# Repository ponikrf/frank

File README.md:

# FRANK

FRANK is a versatile hardware emulation platform based on Raspberry Pico and Raspberry Zero. It is a hardware fork of the [Murmulator](https://murmulator.ru/) project by [Alex Ekb](https://t.me/Alex_Eburg), incorporating numerous additional features.

The name "FRANK" is derived from "Frankenstein" as it integrates various components from different projects, similar to how Dr. Frankenstein created his monster from different parts. This combination enables FRANK to offer a unique and powerful set of capabilities.

## Supported Platforms

FRANK supports emulation for a variety of platforms, including:

* ZX Spectrum (48K, 128K and other models, including clones)
* IBM PC XT 8088
* BK-0011М (soviet 8 bit home computer)
* Radio 86RK (soviet 8 bit home computer)
* Atari 800
* NES/Famicom (also known as Dendy)
* Sega Master System
* Sega Game Gear
* NEC PC Engine / TurboGrafx 16
* Sega MegaDrive / Genesis
* Nintendo GameBoy
* Nintendo GameBoy Color
* Watara Supervision
* Atari Lynx
* Bandai Wonderswan
* NeoGeo Pocket Color
* Picomite MMBasic
* VersaTerm
* DOOM
* Macintosh 512K
* MurmulatorOS

## FRANK Models

Currently there are the following versions of FRANK available:

* [FRANK M1](./hardware/frank_m1) (latest hardware revision: 1.17)
* [FRANK M2](./hardware/frank_m2) (latest hardware revision: 1.03)
* [MiniFRANK RM1](./hardware/minifrank_rm1) (latest hardware revision: 2.07)
* [TurboFRANK](./hardware/turbofrank) (latest hardware revision: 1.07)

## Side Projects

* [HDMI2VGA](./hardware/hdmi2vga) - HDMI to VGA/Soft Composite passive adaptor (latest hardware revision: 2.03)
* [USB2PS2](./hardware/usb2ps2) - USB to PS/2 adapter built on RP2040-Zero (latest hardware revision: 1.03)

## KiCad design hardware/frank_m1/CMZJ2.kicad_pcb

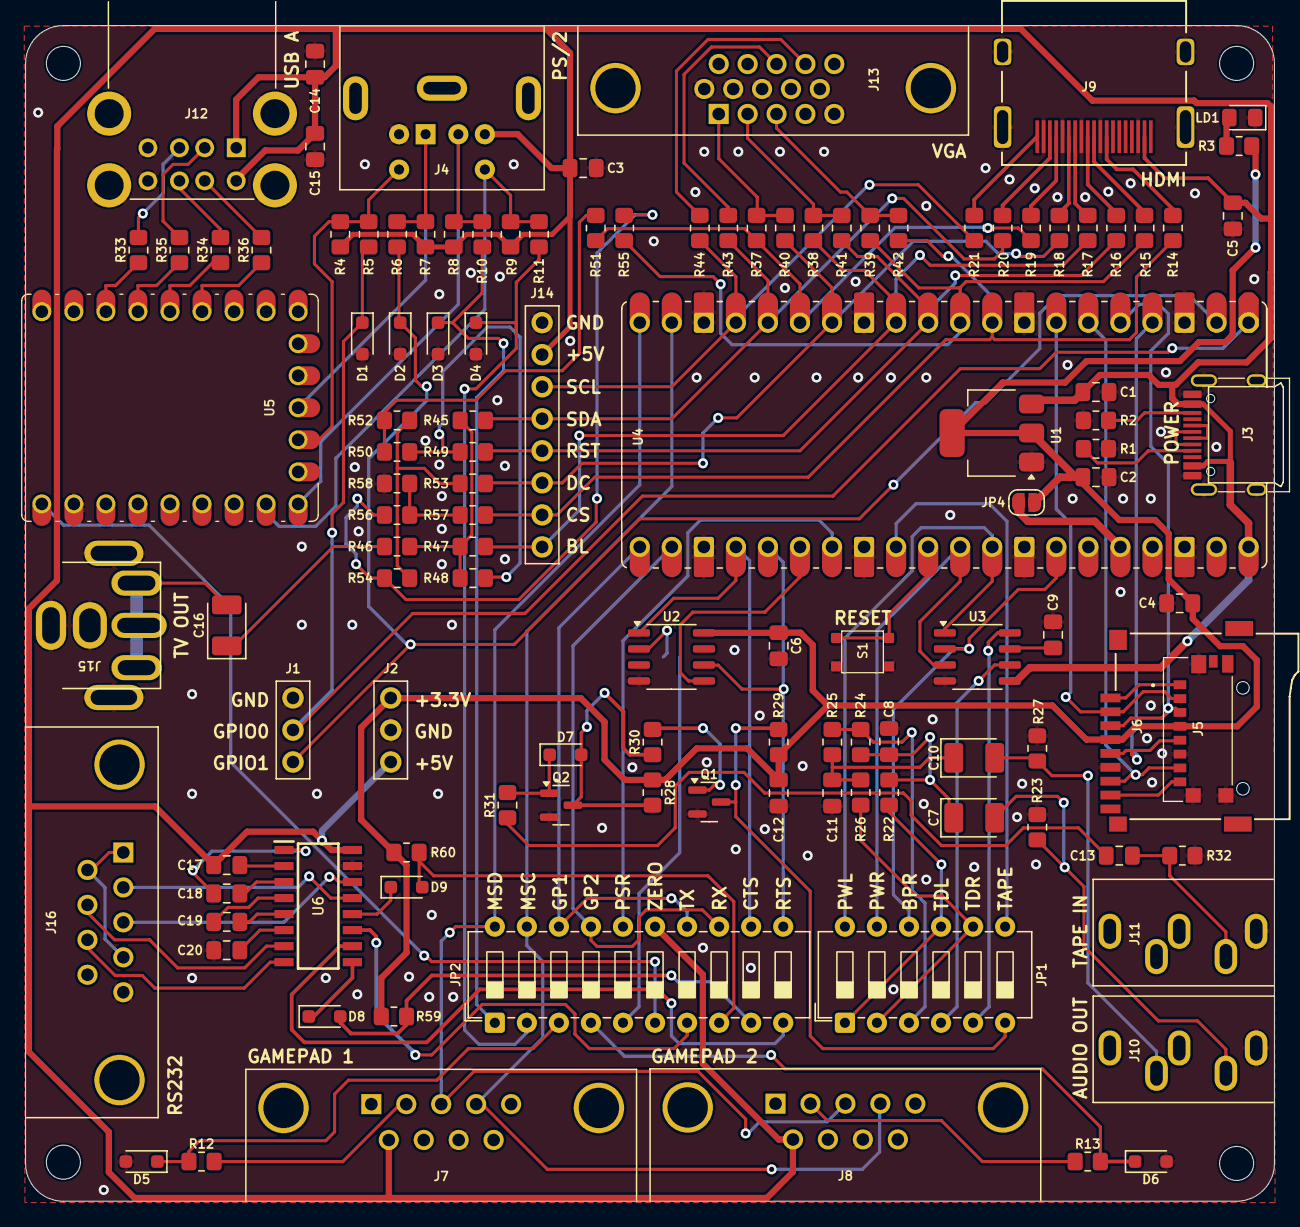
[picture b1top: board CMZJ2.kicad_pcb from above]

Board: 2 copper layers, 99.0 x 93.2 mm, 123 parts (1 on the bottom side), 113 nets.

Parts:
C1, C2, C9, C14, C15: 10u; Capacitor (0805)
C3, C4, C5, C6, C12, C13: 100n; Capacitor (0805)
C7, C10: 10u; Capacitor (3528, tantalum, polar)
C8, C11: 10n; Capacitor (0805)
C16: 220u; Capacitor (3528, tantalum, polar)
C17, C18, C19, C20: 1u; Capacitor (0805)
D1, D2, D3, D4, D5, D6: 3V3; Diode (SOD-323)
D7, D8, D9: 1N4148; Diode (SOD-323)
H1, H2, H3, H4: Hole 2.7mm; Mounting Hole (2.7mm)
J1, J2: Pin Header 1x03; Pin Header (1x03)
J3: USB4215; USB Type C
J4: MDC-036; MiniDIN (6 Pin, female)
J5: 0475710001; MicroSD (SMD, short)
J6: 104031-0811; MicroSD (SMD, long)
J7, J8, J16: D-SUB 9 Male; D-SUB (9 pin, male, top mount)
J9: DC3RX19JA2; HDMI (female)
J10, J11: SJ1-353XNG; Jack (3.5mm)
J12: SS-52100-004; USB Type A (stacked)
J13: D-SUB 15 Female; D-SUB (15 pin, female)
J14: Pin Header 1x08; Pin Header (1x08)
J15: RCA-103; RCA
JP1: SW_DIP_x06; DIP Switch (6)
JP2: SW_DIP_x10; DIP Switch (10)
JP3, JP4: Jumper (Solder); Jumper (solder)
LD1: Green; LED (0805)
Q1, Q2: BC850; SOT-23
R1, R2: 5.1K; Resistor (0805)
R3, R4, R7, R8, R9, R12, R13, R22, R26, R29, R40, R41, R42, R59, R60: 1K; Resistor (0805)
R5, R6, R10, R11, R32, R43, R44: 100R; Resistor (0805)
R14, R15, R16, R17, R18, R19, R20, R21, R47, R49, R51, R53, R55, R57: 270R; Resistor (0805)
R23, R27, R37, R38, R39: 330R; Resistor (0805)
R24, R25: 2K; Resistor (0805)
R28, R30, R31: 10K; Resistor (0805)
R33, R34, R35, R36: 22R; Resistor (0805)
R45: 750R; Resistor (0805)
R46: 51R; Resistor (0805)
R48, R50, R52, R54, R56: 150R; Resistor (0805)
R58: 300R; Resistor (0805)
S1: TS-1233; Button (SMD, 3x3mm, 1-1)
U1: NCP1117 3.3; SOT-223
U2: ESP-PSRAM32; SO-8
U3: TDA1387T; SO-8
U4: Rasberry Pi Pico; Raspberry Pi Pico
U5: RP2040-Zero; Raspberry Pi Zero
U6: MAX232CSE+; SOIC127P600X175-16N

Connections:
+3V3: C2.1, C4.2, C6.1, C12.1, J2.1, J5.P4 (VDD), J6.4 (VDD), JP4.2 (B), R3.2, R28.1, R29.1, R59.2, R60.2, U1.2 (VO), U2.8 (VCC)
/A_OUTB: JP1.3, R24.2, R25.2
/A_OUTL: JP1.1, JP1.9, R22.2
/A_OUTR: JP1.2, JP1.8, R26.2
/A_TDAL: JP1.4, U3.6 (A_LEFT)
/A_TDAR: JP1.5, U3.8 (A_RIGHT)
/Audio Out/L: C7.2, J10.T, R23.1
/Audio Out/R: C10.2, J10.R, R27.1
/Composite/CVBS: C16.2, J15.1
/GP1_DATA: D5.1 (K), JP2.3, R12.1
/GP2_DATA: D6.1 (K), JP2.4, R13.1
/GPIO0: D1.1 (K), J1.2, R5.2, U4.1 (GPIO0)
/GPIO1: D2.1 (K), J1.3, R6.2, U4.2 (GPIO1)
/GPIO2: J5.P5 (CLK), J6.5 (CLK), U4.4 (GPIO2)
/GPIO3: J5.P3 (CMD), J6.3 (CMD), U4.5 (GPIO3)
/GPIO4: J5.P7 (DAT0), J6.7 (DAT0), U4.6 (GPIO4)
/GPIO5: J5.P2 (CD/DAT3), J6.2 (DAT3/CD), U4.7 (GPIO5)
/GPIO6: J14.7, R14.2, R42.1, R57.1, U4.9 (GPIO6)
/GPIO7: R15.2, R39.1, R55.1, U4.10 (GPIO7)
/GPIO8: J14.5, R16.2, R41.1, R49.1, U4.11 (GPIO8)
/GPIO9: J14.8, R17.2, R38.1, R47.1, U4.12 (GPIO9)
/GPIO10: J14.6, R18.2, R40.1, R53.1, U4.14 (GPIO10)
/GPIO11: R19.2, R37.1, R51.1, U4.15 (GPIO11)
/GPIO12: J14.4, R20.2, R43.2, R45.1, U4.16 (GPIO12)
/GPIO13: J14.3, R21.2, R44.2, U4.17 (GPIO13)
/GPIO14: J7.4, J8.4, JP2.19, U4.19 (GPIO14)
/GPIO15: J7.3, J8.3, JP2.20, U4.20 (GPIO15)
/GPIO16: JP2.14, JP2.18, U4.21 (GPIO16)
/GPIO17: JP2.13, JP2.17, U4.22 (GPIO17)
/GPIO18: JP2.12, U2.1 (~CE), U4.24 (GPIO18)
/GPIO19: JP2.11, U2.6 (SCLK), U4.25 (GPIO19)
/GPIO20: U2.5 (SI/SIO), U4.26 (GPIO20)
/GPIO21: JP2.16, U4.27 (GPIO21)
/GPIO22: JP1.7, U4.29 (GPIO22)
/GPIO26: JP1.11, U3.3 (DATA), U4.31 (GPIO26_ADC0)
/GPIO27: JP1.12, U3.1 (SCLK), U4.32 (GPIO27_ADC1)
/GPIO28: JP1.10, U3.2 (LRCK), U4.34 (GPIO28_ADC2)
/KB_CLK: J4.5, R4.2, R5.1, U5.13 (12)
/KB_DATA: J4.1, R6.1, R7.2, U5.12 (11)
/LOAD_IN_D: JP1.6, Q1.3 (C), R29.2
/MS_CLK: J4.6, R9.2, R11.1, U5.16 (15)
/MS_CLK_3V: D4.1 (K), JP2.2, R11.2
/MS_DATA: J4.2, R8.2, R10.1, U5.15 (14)
/MS_DATA_3V: D3.1 (K), JP2.1, R10.2
/Micro SD/DAT1: J5.P8 (DAT1), J6.8 (DAT1)
/Micro SD/DAT2: J5.P1 (DAT2), J6.1 (DAT2)
/PSR_SOSIO: JP2.5, JP3.2 (B)
/Power/D+: J3.6 (DP1), J3.8 (DP2)
/Power/D-: J3.5 (DN2), J3.7 (DN1)
/RS232/C1+: C18.2, U6.1 (C1+)
/RS232/C1-: C18.1, U6.3 (C1-)
/RS232/C2+: C19.2, U6.4 (C2+)
/RS232/C2-: C19.1, U6.5 (C2-)
/RS232/CTS_IN: J16.7, U6.7 (T2OUT)
/RS232/CTS_MAX: D8.1 (K), U6.9 (R2OUT)
/RS232/RTS_IN: J16.8, U6.8 (R2IN)
/RS232/RX_IN: J16.3, U6.14 (T1OUT)
/RS232/RX_MAX: D9.1 (K), U6.12 (R1OUT)
/RS232/TX_IN: J16.2, U6.13 (R1IN)
/RS232/V+: C17.1, U6.2 (V+)
/RS232/V-: C20.1, U6.6 (V-)
/RS232_CTS: D8.2 (A), JP2.9, R59.1
/RS232_RTS: JP2.10, U6.10 (T2IN)
/RS232_RX: D9.2 (A), JP2.8, R60.1
/RS232_TX: JP2.7, U6.11 (T1IN)
/RUN: S1.1, U4.30 (RUN)
/USB_D1M: R35.1, U5.4 (3)
/USB_D1P: R33.1, U5.3 (2)
/USB_D2M: R36.1, U5.6 (5)
/USB_D2P: R34.1, U5.5 (4)
/ZERO_VBUS: JP2.6, U5.23 (5V)
GND: C1.2, C2.2, C3.2, C4.1, C5.2, C6.2, C8.2, C9.2, C11.2, C12.2, C14.2, C15.2, C20.2, D1.2 (A), D2.2 (A), D3.2 (A), D4.2 (A), D5.2 (A), D6.2 (A), J1.1, J2.2, J3.1 (GND), J3.12 (GND), J3.13 (SHIELD), J4.3, J5.G1 (GND_1), J5.G2 (GND_2), J5.G3 (GND_3), J5.P6 (VSS), J6.6 (VSS), J7.8, J8.8, J9.2 (G_D2), J9.5 (G_D1), J9.8 (G_D0), J9.11 (G_CLK), J9.17 (G_DDC/CEC), J9.20 (SHIELD1), J9.21 (SHIELD2), J9.22 (SHIELD3), J9.23 (SHIELD4), J10.S, J11.S, J12.4 (GND1), J12.8 (GND2), J12.9 (Shield), J13.0, J13.5, J13.6, J13.7, J13.8, J13.10, J14.1, J15.2, J16.5, LD1.1 (K), Q1.2 (E), Q2.2 (E), R1.1, R2.1, R23.2, R27.2, R32.2, R58.1, S1.2, U1.1 (GND), U2.4 (VSS), U3.4 (AGND), U4.3 (GND), U4.8 (GND), U4.13 (GND), U4.18 (GND), U4.23 (GND), U4.28 (GND), U4.33 (AGND), U4.38 (GND), U5.22 (GND), U6.15 (GND)
unnamed: C7.1, C8.1, R22.1, R24.1
unnamed: C10.1, C11.1, R25.1, R26.1
unnamed: C13.1, J11.T, R32.1
unnamed: C13.2, R31.1
unnamed: C16.1, R46.2
unnamed: D7.2 (A), Q2.3 (C), R28.2, R30.1
unnamed: D7.1 (K), Q2.1 (B), R31.2
unnamed: J3.4 (CC1), R1.2
unnamed: J3.10 (CC2), R2.2
unnamed: J7.2, R12.2
unnamed: J8.2, R13.2
unnamed: J9.12 (CLKN), R14.1
unnamed: J9.10 (CLKP), R15.1
unnamed: J9.9 (D0N), R16.1
unnamed: J9.7 (D0P), R17.1
unnamed: J9.6 (D1N), R18.1
unnamed: J9.4 (D1P), R19.1
unnamed: J9.3 (D2N), R20.1
unnamed: J9.1 (D2P), R21.1
unnamed: J12.3 (D1+), R33.2
unnamed: J12.2 (D1-), R35.2
unnamed: J12.7 (D2+), R34.2
unnamed: J12.6 (D2-), R36.2
unnamed: J13.1, R37.2, R40.2
unnamed: J13.2, R38.2, R41.2
unnamed: J13.3, R39.2, R42.2
unnamed: J13.13, R43.1
unnamed: J13.14, R44.1
unnamed: J16.1, J16.4, J16.6
unnamed: JP3.1 (A), U2.2 (SO/SIO)
unnamed: JP4.1 (A), U4.36 (3V3)
unnamed: LD1.2 (A), R3.1
unnamed: Q1.1 (B), R30.2
unnamed: R45.2, R46.1, R47.2, R48.2
unnamed: R48.1, R49.2, R50.2
unnamed: R50.1, R51.2, R52.2
unnamed: R52.1, R53.2, R54.2
unnamed: R54.1, R55.2, R56.2
unnamed: R56.1, R57.2, R58.2
unnamed: C9.1, U3.7 (FLT)
VBUS: C1.1, C3.1, C5.1, C14.1, C15.1, C17.2, J2.3, J3.2 (VBUS), J3.11 (VBUS), J4.4, J7.6, J8.6, J9.18 (+5V), J12.1 (VBUS1), J12.5 (VBUS2), J14.2, JP2.15, R4.1, R7.1, R8.1, R9.1, U1.3 (VI), U3.5 (VA), U4.40 (VBUS), U6.16 (VCC)

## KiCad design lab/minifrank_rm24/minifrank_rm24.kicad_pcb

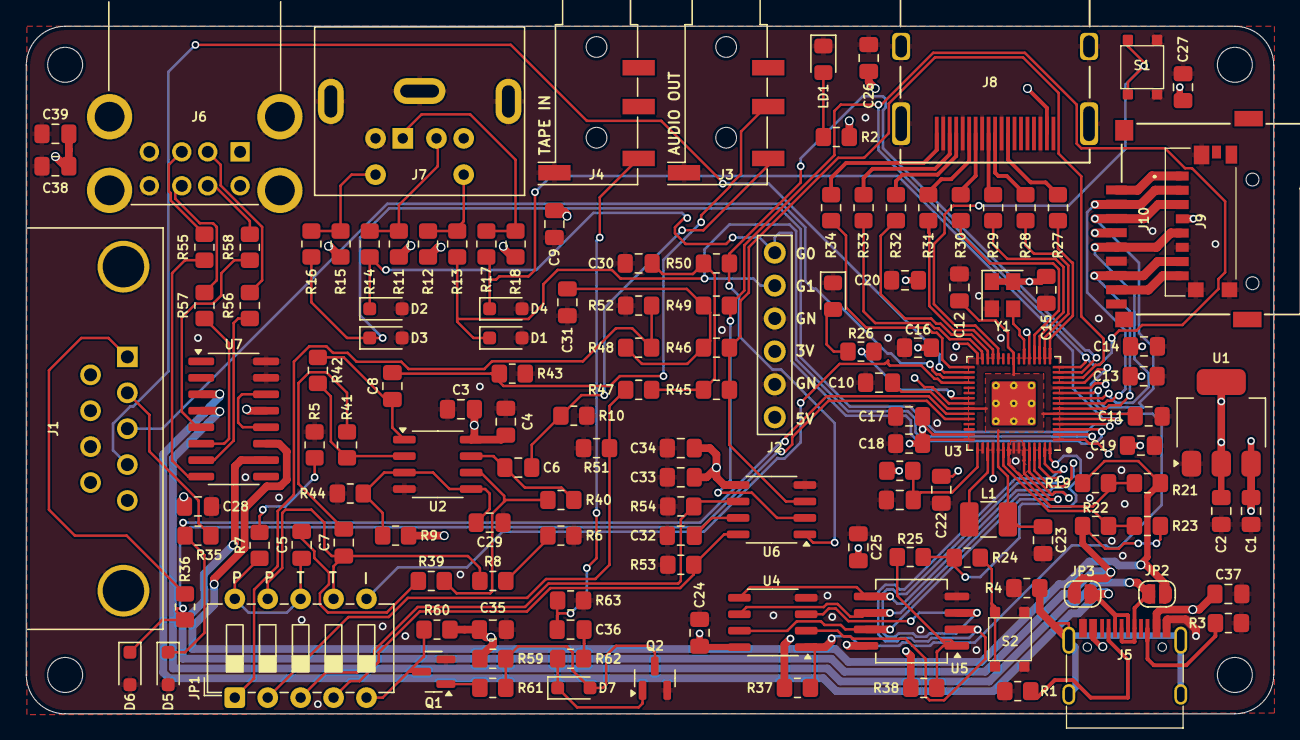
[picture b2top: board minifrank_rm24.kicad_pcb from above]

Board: 4 copper layers, 96.2 x 53.0 mm, 141 parts (0 on the bottom side), 104 nets.

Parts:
C1, C2, C3, C5, C6, C7, C8, C9, C29, C32, C33, C38, C39: 10u; Capacitor (0805)
C4, C10, C12, C13, C14, C15, C16, C17, C18, C19, C20, C24, C25, C26, C27, C28, C34, C35, C36: 100n; Capacitor (0805)
C11, C21, C22, C23, C37: 4.7u; Capacitor (0805)
C30, C31: 47n; Capacitor (0805)
D1, D2, D3, D4, D5, D6: 3V3; Diode (SOD-323)
D7: 1N4148; Diode (SOD-323)
H1, H2, H3, H4: MountingHole; Mounting Hole (2.7mm)
J1: Gamepad; D-SUB (9 pin, male, top mount)
J2: Connectors; Pin Header (1x06)
J3, J4: PJ-320D; Jack (3.5mm, PJ-320D)
J5: USB4215-03-A; USB Type C
J6: SS-52100-004; USB Type A (stacked)
J7: Mini-DIN-6; MiniDIN (6 Pin, female)
J8: HDMI Female; HDMI (female)
J9: 47571-0001; MicroSD (SMD, short)
J10: 104031-0811; MicroSD (SMD, long)
JP1: SD04H0SB; DIP Switch (5x5)
JP2, JP3: Jumper (Solder); Jumper (solder)
L1: 3.3u; Inductor (3225)
LD1: Green; LED (0805)
LD2: Blue; LED (0805)
Q1, Q2: BC850; SOT-23
R1, R3: 5.1K; Resistor (0805)
R2, R11, R12, R15, R24, R26, R35, R36, R49, R50, R60: 1K; Resistor (0805)
R4: 1M; Resistor (0805)
R5, R6, R45, R46, R51, R52: 2K; Resistor (0805)
R7, R8, R9, R37, R38, R39, R41, R44, R47, R48, R59, R61, R62: 10K; Resistor (0805)
R10, R43: 20K; Resistor (0805)
R13, R14, R16, R17, R63: 100R; Resistor (0805)
R18: 1k; Resistor (0805)
R19, R22: 150R; Resistor (0805)
R20: 33; Resistor (0805)
R21, R23: 33R; Resistor (0805)
R25: 0; Resistor (0805)
R27, R28, R29, R30, R31, R32, R33, R34: 270R; Resistor (0805)
R40, R42: 47K; Resistor (0805)
R53, R54: 470R; Resistor (0805)
R55, R56, R57, R58: 22R; Resistor (0805)
S1, S2: TS-1233; Button (SMD, 3x3mm, 1-1)
U1: NCP1117 3.3; SOT-223
U2: LM358; SO-8
U3: RP2350; QFN 60 (RP2350A)
U4: ESP-PSRAM32; SO-8
U5: W25Q128JVS; SOIC-8
U6: TDA1387T; SO-8
U7: MW7211A; SOP-16
Y1: ASE-12MHz; Crystal (3225, active)

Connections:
+1V1: C10.1, C11.1, C12.1, C23.1, L1.1, U3.6 (DVDD), U3.23 (DVDD), U3.39 (DVDD), U3.50 (VREG_FB)
+3V3: C2.1, C13.1, C14.1, C15.1, C16.1, C17.1, C18.1, C19.1, C20.1, C22.1, C24.1, C25.1, C27.2, C35.1, J2.3, J9.P4 (VDD), J10.4 (VDD), R2.2, R20.1, R37.2, R38.1, R59.1, R60.1, U1.2 (VO), U3.1 (IOVDD), U3.11 (IOVDD), U3.20 (IOVDD), U3.30 (IOVDD), U3.38 (IOVDD), U3.44 (ADC_AVDD), U3.45 (IOVDD), U3.49 (VREG_VIN), U3.53 (USB_OTP_VDD), U3.54 (QSPI_IOVDD), U4.8 (VCC), U5.8 (VCC), Y1.1 (EN), Y1.4 (Vdd)
/AMP_OUTL: C5.1, JP1.2, JP1.6, R7.1
/AMP_OUTR: C7.1, JP1.4, JP1.8, R8.1
/Audio Out/AMP_OUTL: C6.2, J3.T, R10.2
/Audio Out/AMP_OUTR: C8.2, J3.R, R43.2
/D+: JP2.2 (B), R19.1, R21.1, U7.11 (DPU)
/D-: JP3.2 (B), R22.1, R23.1, U7.10 (DMU)
/GPIO0: D1.1 (K), J2.5, R13.2, U3.2 (GPIO0)
/GPIO1: D2.1 (K), J2.6, R14.2, U3.3 (GPIO1)
/GPIO2: D3.1 (K), R16.2, U3.4 (GPIO2)
/GPIO3: D4.1 (K), R17.2, U3.5 (GPIO3)
/GPIO4: J9.P7 (DAT0), J10.7 (DAT0), U3.7 (GPIO4)
/GPIO5: J9.P2 (CD/DAT3), J10.2 (DAT3/CD), U3.8 (GPIO5)
/GPIO6: J9.P5 (CLK), J10.5 (CLK), U3.9 (GPIO6)
/GPIO7: J9.P3 (CMD), J10.3 (CMD), U3.10 (GPIO7)
/GPIO8: R37.1, U3.12 (GPIO8), U4.1 (~CE)
/GPIO9: R45.1, R46.1, U3.13 (GPIO9), U6.3 (DATA)
/GPIO10: R50.2, U3.14 (GPIO10), U6.1 (SCLK)
/GPIO11: R49.2, U3.15 (GPIO11), U6.2 (LRCK)
/GPIO12: R27.2, U3.16 (GPIO12)
/GPIO13: R28.2, U3.17 (GPIO13)
/GPIO14: R29.2, U3.18 (GPIO14)
/GPIO15: R30.2, U3.19 (GPIO15)
/GPIO16: R31.2, U3.27 (GPIO16)
/GPIO17: R32.2, U3.28 (GPIO17)
/GPIO18: R33.2, U3.29 (GPIO18)
/GPIO19: R34.2, U3.31 (GPIO19)
/GPIO20: J1.4, U3.32 (GPIO20)
/GPIO21: J1.3, U3.33 (GPIO21)
/GPIO22: JP1.10, U3.34 (GPIO22)
/GPIO26: D5.1 (K), R35.1, U3.40 (GPIO26_ADC0)
/GPIO27: D6.1 (K), R36.1, U3.41 (GPIO27_ADC1)
/Gamepad/J1_DATA: J1.2, R35.2
/Gamepad/J2_DATA: J1.1, R36.2
/LOAD_IN: JP1.9, Q1.3 (C), R60.2
/PS2/PS/2 CLK: J7.5, R15.2, R16.1
/PS2/PS/2 DATA: J7.1, R17.1, R18.2
/PWM_OUT_L: JP1.1, R48.2, R52.1
/PWM_OUT_R: JP1.3, R47.2, R51.1
/RP2350A/FLASH_SS: R25.2, R38.2, U5.1 (~CS)
/RP2350A/QSPI_SCLK: U3.56 (QSPI_SCLK), U4.6 (SCLK), U5.6 (CLK)
/RP2350A/QSPI_SD0: U3.57 (QSPI_SD0), U4.5 (SI/SIO), U5.5 (DI(IO0))
/RP2350A/QSPI_SD1: U3.59 (QSPI_SD1), U4.2 (SO/SIO), U5.2 (DO(IO1))
/RP2350A/QSPI_SD2: U3.58 (QSPI_SD2), U4.3 (SIO2), U5.3 (IO2)
/RP2350A/QSPI_SD3: U3.55 (QSPI_SD3), U4.7 (SIO3), U5.7 (IO3)
/RP2350A/QSPI_SS: R24.1, R25.1, U3.60 (QSPI_SS)
/RP2350A/VREG_AVDD: C21.1, R20.2, U3.46 (VREG_AVDD)
/RP2350A/VREG_LX: L1.2, U3.48 (VREG_LX)
/RP2350A/XIN: U3.21 (XIN), Y1.3 (OUT)
/RP2350A/~USB_BOOT: R24.2, S2.2
/RUN: S1.1, U3.26 (RUN)
/SD Card/DAT1: J9.P8 (DAT1), J10.8 (DAT1)
/SD Card/DAT2: J9.P1 (DAT2), J10.1 (DAT2)
/TDA_OUT_L: JP1.5, R54.2, U6.6 (A_LEFT)
/TDA_OUT_R: JP1.7, R53.1, U6.8 (A_RIGHT)
/USB_D1+: R55.1, U7.8 (DP3)
/USB_D1-: R56.1, U7.7 (DM3)
/USB_D2+: R57.1, U7.6 (DP2)
/USB_D2-: R58.1, U7.5 (DM2)
/USB_D3+: J5.6 (DP1), J5.8 (DP2), JP2.1 (A), U7.4 (DP1)
/USB_D3-: J5.5 (DN2), J5.7 (DN1), JP3.1 (A), U7.3 (DM1)
GND: C1.2, C2.2, C3.1, C4.1, C9.2, C10.2, C11.2, C12.2, C13.2, C14.2, C15.2, C16.2, C17.2, C18.2, C19.2, C20.2, C21.2, C22.2, C23.2, C24.2, C25.2, C26.2, C27.1, C28.2, C29.1, C30.2, C31.2, C32.2, C33.2, C34.2, C35.2, C37.2, C38.2, C39.2, D1.2 (A), D2.2 (A), D3.2 (A), D4.2 (A), D5.2 (A), D6.2 (A), J1.8, J2.2, J2.4, J3.S, J4.S, J5.1 (GND), J5.12 (GND), J6.4 (GND1), J6.8 (GND2), J6.9 (Shield), J7.3, J8.2 (G_D2), J8.5 (G_D1), J8.8 (G_D0), J8.11 (G_CLK), J8.17 (G_DDC/CEC), J8.20 (SHIELD1), J8.21 (SHIELD2), J8.22 (SHIELD3), J8.23 (SHIELD4), J9.G1 (GND_1), J9.G2 (GND_2), J9.G3 (GND_3), J9.P6 (VSS), J10.6 (VSS), LD1.1 (K), LD2.1 (K), Q1.2 (E), Q2.2 (E), R1.1, R3.1, R4.2, R5.2, R6.2, R10.1, R43.1, R44.1, R51.2, R52.2, R53.2, R54.1, R63.2, S1.2, S2.1, U1.1 (GND), U2.4 (V-), U3.47 (VREG_PGND), U3.61 (GND), U4.4 (VSS), U5.4 (GND), U6.4 (AGND), U7.15 (GND), U7.16 (GND), Y1.2 (GND)
GPIO25: R26.2, U3.37 (GPIO25)
unnamed: C5.2, R39.2
unnamed: C6.1, R40.1, U2.7
unnamed: C7.2, R41.2
unnamed: C8.1, R42.1, U2.1
unnamed: C30.1, R45.2, R47.1, R50.1
unnamed: C31.1, R46.2, R48.1, R49.1
unnamed: C36.1, J4.T, R63.1
unnamed: C36.2, R62.1
unnamed: D7.2 (A), Q2.3 (C), R59.2, R61.1
unnamed: D7.1 (K), Q2.1 (B), R62.2
unnamed: J5.4 (CC1), R1.2
unnamed: J5.10 (CC2), R3.2
unnamed: J5.13 (SHIELD), R4.1
unnamed: J6.3 (D1+), R55.2
unnamed: J6.2 (D1-), R56.2
unnamed: J6.7 (D2+), R57.2
unnamed: J6.6 (D2-), R58.2
unnamed: J7.2, R11.2, R14.1
unnamed: J7.6, R12.2, R13.1
unnamed: J8.12 (CLKN), R27.1
unnamed: J8.10 (CLKP), R28.1
unnamed: J8.9 (D0N), R29.1
unnamed: J8.7 (D0P), R30.1
unnamed: J8.6 (D1N), R31.1
unnamed: J8.4 (D1P), R32.1
unnamed: J8.3 (D2N), R33.1
unnamed: J8.1 (D2P), R34.1
unnamed: LD1.2 (A), R2.1
unnamed: LD2.2 (A), R26.1
unnamed: Q1.1 (B), R61.2
unnamed: R5.1, R7.2
unnamed: R6.1, R8.2
unnamed: C29.2, R9.1, R44.2, U2.3 (+), U2.5 (+)
unnamed: R41.1, R42.2, U2.2 (-)
unnamed: R39.1, R40.2, U2.6 (-)
unnamed: R22.2, R23.2, U3.51 (USB_DM)
unnamed: R19.2, R21.2, U3.52 (USB_DP)
unnamed: C32.1, U6.7 (FLT)
unnamed: U7.12 (VD33), U7.14 (VD3)
VBUS: C1.1, C3.2, C4.2, C9.1, C26.1, C28.1, C33.1, C34.1, C37.1, C38.1, C39.1, J1.6, J2.1, J5.2 (VBUS), J5.11 (VBUS), J6.1 (VBUS1), J6.5 (VBUS2), J7.4, J8.18 (+5V), R9.2, R11.1, R12.1, R15.1, R18.1, U1.3 (VI), U2.8 (V+), U6.5 (VA), U7.13 (VDD5)

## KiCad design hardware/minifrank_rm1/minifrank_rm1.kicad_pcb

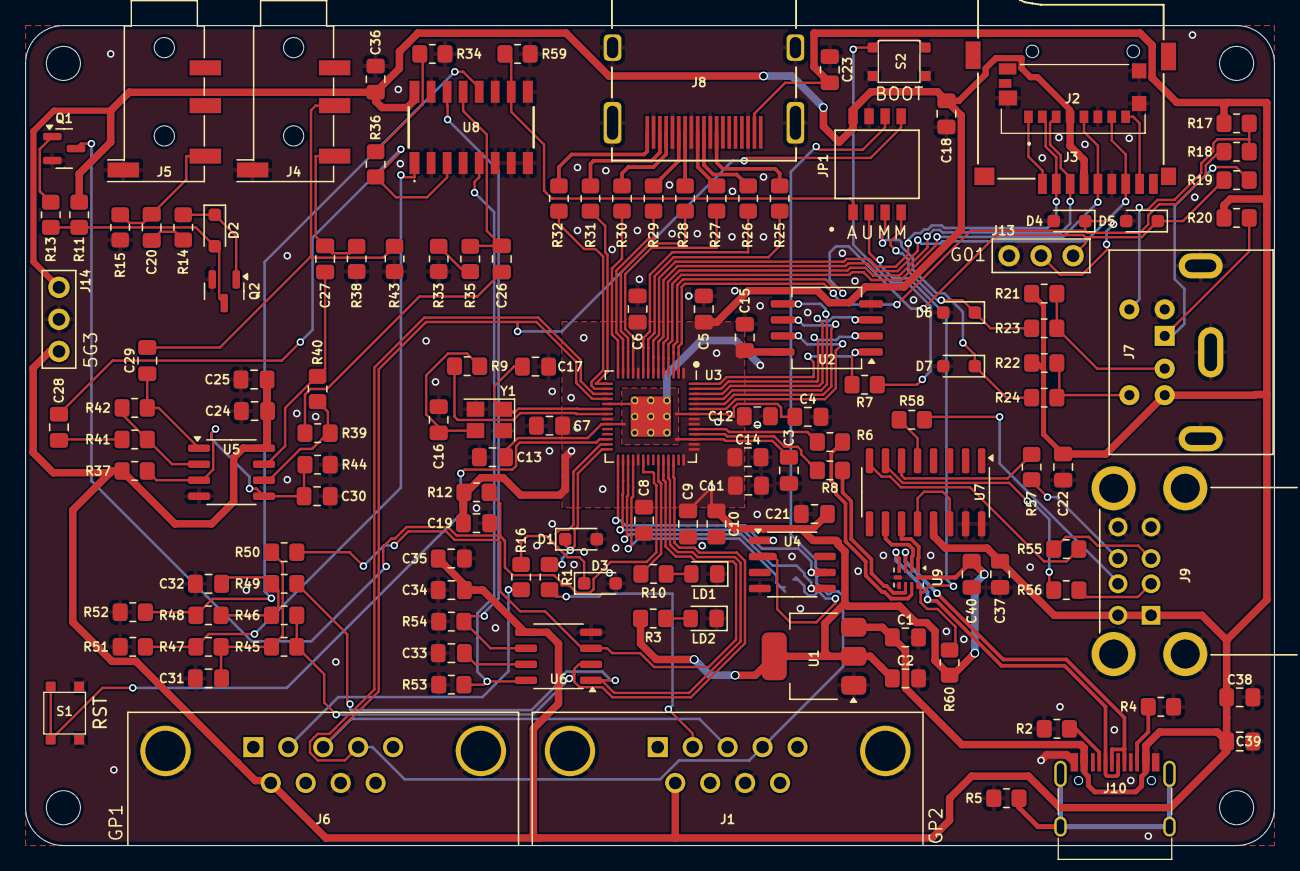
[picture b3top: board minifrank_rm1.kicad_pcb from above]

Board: 2 copper layers, 99.0 x 65.0 mm, 141 parts (1 on the bottom side), 110 nets.

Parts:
C1, C2, C24, C26, C27, C28, C29, C30, C33, C34, C38, C39: 10u; Capacitor (0805)
C3, C4, C5, C6, C7, C8, C9, C10, C11, C12, C15, C18, C19, C20, C21, C22, C23, C25, C35, C36, C40: 100n; Capacitor (0805)
C13, C14: 1u; Capacitor (0805)
C16, C17: 15p; Capacitor (0805)
C31, C32: 47n; Capacitor (0805)
C37: 4.7u; Capacitor (0805)
D1, D3, D4, D5, D6, D7: 3V3; Diode (SOD-323)
D2: 1N4148; Diode (SOD-323)
H1, H2, H3, H4: MountingHole; Mounting Hole (2.7mm)
J1, J6: D-SUB 9 Male; D-SUB (9 pin, male, top mount)
J2: 0475710001; MicroSD (SMD, short)
J3: 104031-0811; MicroSD (SMD, long)
J4, J5: PJ-320D; Jack (3.5mm, PJ-320D)
J7: MDC-036; MiniDIN (6 Pin, female)
J8: DC3RX19JA2; HDMI (female)
J9: SS-52100-004; USB Type A (stacked)
J10: USB4215-03-A; USB Type C
J13: UART; Pin Header (1x03)
J14: PWR; Pin Header (1x03)
JP1: Main Jumpers; SW_DS05-127-2-04BK-SMT-TR
JP2: Jumper (Solder); Jumper (solder)
LD1: Blue; LED (0805)
LD2: Green; LED (0805)
Q1, Q2: BC850; SOT-23
R1, R3, R7, R9, R10, R12, R16, R17, R20, R21, R22, R49, R50: 1K; Resistor (0805)
R2, R4: 5.1K; Resistor (0805)
R5: 1M; Resistor (0805)
R6, R8: 27R; Resistor (0805)
R11, R13, R14, R35, R36, R37, R39, R41, R44, R47, R48, R59, R60: 10K; Resistor (0805)
R15, R18, R19, R23, R24: 100R; Resistor (0805)
R25, R26, R27, R28, R29, R30, R31, R32: 270R; Resistor (0805)
R33, R34, R45, R46, R51, R52: 2K; Resistor (0805)
R38, R43: 20K; Resistor (0805)
R40, R42: 47K; Resistor (0805)
R53, R54: 470R; Resistor (0805)
R55, R56, R57, R58: 22R; Resistor (0805)
S1: Reset; Button (SMD, 3x3mm, 1-1)
S2: Boot; Button (SMD, 3x3mm, 1-1)
U1: NCP1117 3.3; SOT-223
U2: W25Q128JVSIQ; SOIC-8
U3: RP2040; QFN 56
U4: ESP-PSRAM32; SO-8
U5: LM358; SO-8
U6: TDA1387T; SO-8
U7: MW7211A; SOP-16
U8: 74HC4052D; 74HC4052D653
U9: TS3USB221RSER; UQFN-10
Y1: 12 MHz; Crystal (3225)

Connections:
+3V3: C2.1, C5.1, C6.1, C7.1, C8.1, C9.1, C10.1, C11.1, C12.1, C14.1, C15.1, C18.2, C19.1, C21.1, C36.2, C40.2, J2.P4 (VDD), J3.4 (VDD), J14.1, JP1.8, R3.2, R11.1, R12.1, R60.1, U1.2 (VO), U2.8 (VCC), U3.1 (IOVDD), U3.10 (IOVDD), U3.22 (IOVDD), U3.33 (IOVDD), U3.42 (IOVDD), U3.43 (ADC_AVDD), U3.44 (VREG_IN), U3.48 (USB_VDD), U3.49 (IOVDD), U4.8 (VCC), U8.16 (VCC), U9.10 (VCC)
/AMP_IN_L: C26.1, R35.1, U8.13 (1Z)
/AMP_IN_R: C28.1, R36.1, U8.3 (2Z)
/AUDIOSW: JP1.1, R59.2, U8.10 (S0)
/Audio Out/AMP_OUTL: C27.2, J4.T, R38.2
/Audio Out/AMP_OUTR: C29.2, J4.R, R43.2
/D+: R6.1, U9.8 (D+)
/D-: R8.1, U9.7 (D-)
/GPIO0: D4.1 (K), J13.2, R18.2, U3.2 (GPIO0)
/GPIO1: D5.1 (K), J13.3, R19.2, U3.3 (GPIO1)
/GPIO2: J2.P5 (CLK), J3.5 (CLK), U3.4 (GPIO2)
/GPIO3: J2.P3 (CMD), J3.3 (CMD), U3.5 (GPIO3)
/GPIO4: J2.P7 (DAT0), J3.7 (DAT0), U3.6 (GPIO4)
/GPIO5: J2.P2 (CD/DAT3), J3.2 (DAT3/CD), U3.7 (GPIO5)
/GPIO6: R25.2, U3.8 (GPIO6)
/GPIO7: R26.2, U3.9 (GPIO7)
/GPIO8: R27.2, U3.11 (GPIO8)
/GPIO9: R28.2, U3.12 (GPIO9)
/GPIO10: R29.2, U3.13 (GPIO10)
/GPIO11: R30.2, U3.14 (GPIO11)
/GPIO12: R31.2, U3.15 (GPIO12)
/GPIO13: R32.2, U3.16 (GPIO13)
/GPIO14: J1.4, J6.4, JP1.6, U3.17 (GPIO14)
/GPIO15: J1.3, J6.3, JP1.5, U3.18 (GPIO15)
/GPIO16: D3.1 (K), R16.1, U3.27 (GPIO16)
/GPIO17: D1.1 (K), R1.1, U3.28 (GPIO17)
/GPIO18: U3.29 (GPIO18), U4.1 (~CE)
/GPIO19: U3.30 (GPIO19), U4.6 (SCLK)
/GPIO20: U3.31 (GPIO20), U4.5 (SI/SIO)
/GPIO21: JP2.2 (B), U3.32 (GPIO21)
/GPIO22: Q1.3 (C), R12.2, U3.34 (GPIO22)
/GPIO26: R50.2, U3.38 (GPIO26_ADC0), U6.3 (DATA)
/GPIO27: R49.2, U3.39 (GPIO27_ADC1), U6.1 (SCLK)
/GPIO28: R45.1, R46.1, U3.40 (GPIO28_ADC2), U6.2 (LRCK)
/HUB_D+: U7.11 (DPU), U9.1 (1D+)
/HUB_D-: U7.10 (DMU), U9.2 (1D-)
/KB_CLK: J7.5, R17.2, R18.1
/KB_DATA: J7.1, R19.1, R20.2
/MS_CLK: J7.6, R22.2, R24.1
/MS_CLK_3V: D7.1 (K), JP1.3, R24.2
/MS_DATA: J7.2, R21.2, R23.1
/MS_DATA_3V: D6.1 (K), JP1.4, R23.2
/PWM_OUT_L: R48.2, R52.1, U8.12 (1Y0)
/PWM_OUT_R: R47.2, R51.1, U8.1 (2Y0)
/RP2040/GPIO25: R10.2, U3.37 (GPIO25)
/RP2040/QSPI_SCLK: U2.6 (CLK), U3.52 (QSPI_SCLK)
/RP2040/QSPI_SD0: U2.5 (DI(IO0)), U3.53 (QSPI_SD0)
/RP2040/QSPI_SD1: U2.2 (DO(IO1)), U3.55 (QSPI_SD1)
/RP2040/QSPI_SD2: U2.3 (IO2), U3.54 (QSPI_SD2)
/RP2040/QSPI_SD3: U2.7 (IO3), U3.51 (QSPI_SD3)
/RP2040/QSPI_SS: R7.1, U2.1 (~CS), U3.56 (QSPI_SS)
/RP2040/XIN: C17.1, U3.20 (XIN), Y1.1
/RP2040/XOUT: R9.1, U3.21 (XOUT)
/RUN: S1.1, U3.26 (RUN)
/SD Card/DAT1: J2.P8 (DAT1), J3.8 (DAT1)
/SD Card/DAT2: J2.P1 (DAT2), J3.1 (DAT2)
/TDA_L: R54.2, U6.6 (A_LEFT), U8.14 (1Y1)
/TDA_R: R53.1, U6.8 (A_RIGHT), U8.5 (2Y1)
/USBMPXSW: JP1.2, R60.2, U9.9 (S)
/USB_D1+: R55.1, U7.8 (DP3)
/USB_D1-: R56.1, U7.7 (DM3)
/USB_D2+: R57.1, U7.6 (DP2)
/USB_D2-: R58.1, U7.5 (DM2)
/UTC_D+: J10.6 (DP1), J10.8 (DP2), U9.3 (2D+)
/UTC_D-: J10.5 (DN2), J10.7 (DN1), U9.4 (2D-)
GND: C1.2, C2.2, C3.2, C4.2, C5.2, C6.2, C7.2, C8.2, C9.2, C10.2, C11.2, C12.2, C13.2, C14.2, C15.2, C16.2, C17.2, C18.1, C19.2, C21.2, C22.2, C23.2, C24.1, C25.1, C30.1, C31.2, C32.2, C33.2, C34.2, C35.2, C36.1, C37.2, C38.2, C39.2, C40.1, D1.2 (A), D3.2 (A), D4.2 (A), D5.2 (A), D6.2 (A), D7.2 (A), J1.8, J2.G1 (GND_1), J2.G2 (GND_2), J2.G3 (GND_3), J2.P6 (VSS), J3.6 (VSS), J4.S, J5.S, J6.8, J7.3, J8.2 (G_D2), J8.5 (G_D1), J8.8 (G_D0), J8.11 (G_CLK), J8.17 (G_DDC/CEC), J8.20 (SHIELD1), J8.21 (SHIELD2), J8.22 (SHIELD3), J8.23 (SHIELD4), J9.4 (GND1), J9.8 (GND2), J9.9 (Shield), J10.1 (GND), J10.12 (GND), J13.1, J14.2, JP1.7, LD1.1 (K), LD2.1 (K), Q1.2 (E), Q2.2 (E), R2.1, R4.1, R5.2, R15.2, R33.2, R34.2, R38.1, R43.1, R44.1, R51.2, R52.2, R53.2, R54.1, R59.1, S1.2, S2.2, U1.1 (GND), U2.4 (GND), U3.19 (TESTEN), U3.57 (GND), U4.4 (VSS), U5.4 (V-), U6.4 (AGND), U7.15 (GND), U7.16 (GND), U8.2 (2Y2), U8.4 (2Y3), U8.6 (~E), U8.7 (VEE), U8.8 (GND), U8.9 (S1), U8.11 (1Y3), U8.15 (1Y2), U9.5 (GND), U9.6 (~OE), Y1.2, Y1.4
unnamed: C16.1, R9.2, Y1.3
unnamed: C20.1, J5.T, R15.1
unnamed: C20.2, R14.1
unnamed: C26.2, R39.2
unnamed: C27.1, R40.1, U5.7
unnamed: C28.2, R41.2
unnamed: C29.1, R42.1, U5.1
unnamed: C31.1, R45.2, R47.1, R50.1
unnamed: C32.1, R46.2, R48.1, R49.1
unnamed: D2.2 (A), Q2.3 (C), R11.2, R13.1
unnamed: D2.1 (K), Q2.1 (B), R14.2
unnamed: J1.2, R1.2
unnamed: J6.2, R16.2
unnamed: J8.12 (CLKN), R25.1
unnamed: J8.10 (CLKP), R26.1
unnamed: J8.9 (D0N), R27.1
unnamed: J8.7 (D0P), R28.1
unnamed: J8.6 (D1N), R29.1
unnamed: J8.4 (D1P), R30.1
unnamed: J8.3 (D2N), R31.1
unnamed: J8.1 (D2P), R32.1
unnamed: J9.3 (D1+), R55.2
unnamed: J9.2 (D1-), R56.2
unnamed: J9.7 (D2+), R57.2
unnamed: J9.6 (D2-), R58.2
unnamed: J10.4 (CC1), R2.2
unnamed: J10.10 (CC2), R4.2
unnamed: J10.13 (SHIELD), R5.1
unnamed: JP2.1 (A), U4.2 (SO/SIO)
unnamed: LD1.2 (A), R10.1
unnamed: LD2.2 (A), R3.1
unnamed: Q1.1 (B), R13.2
unnamed: R7.2, S2.1
unnamed: R33.1, R35.2
unnamed: R34.1, R36.2
unnamed: R8.2, U3.46 (USB_DM)
unnamed: R6.2, U3.47 (USB_DP)
unnamed: C3.1, C4.1, C13.1, U3.23 (DVDD), U3.45 (VREG_VOUT), U3.50 (DVDD)
unnamed: C30.2, R37.1, R44.2, U5.3 (+), U5.5 (+)
unnamed: R41.1, R42.2, U5.2 (-)
unnamed: R39.1, R40.2, U5.6 (-)
unnamed: C33.1, U6.7 (FLT)
unnamed: U7.12 (VD33), U7.14 (VD3)
VBUS: C1.1, C22.1, C23.1, C24.2, C25.2, C34.1, C35.1, C37.1, C38.1, C39.1, J1.6, J6.6, J7.4, J8.18 (+5V), J9.1 (VBUS1), J9.5 (VBUS2), J10.2 (VBUS), J10.11 (VBUS), J14.3, R17.1, R20.1, R21.1, R22.1, R37.2, U1.3 (VI), U5.8 (V+), U6.5 (VA), U7.13 (VDD5)
